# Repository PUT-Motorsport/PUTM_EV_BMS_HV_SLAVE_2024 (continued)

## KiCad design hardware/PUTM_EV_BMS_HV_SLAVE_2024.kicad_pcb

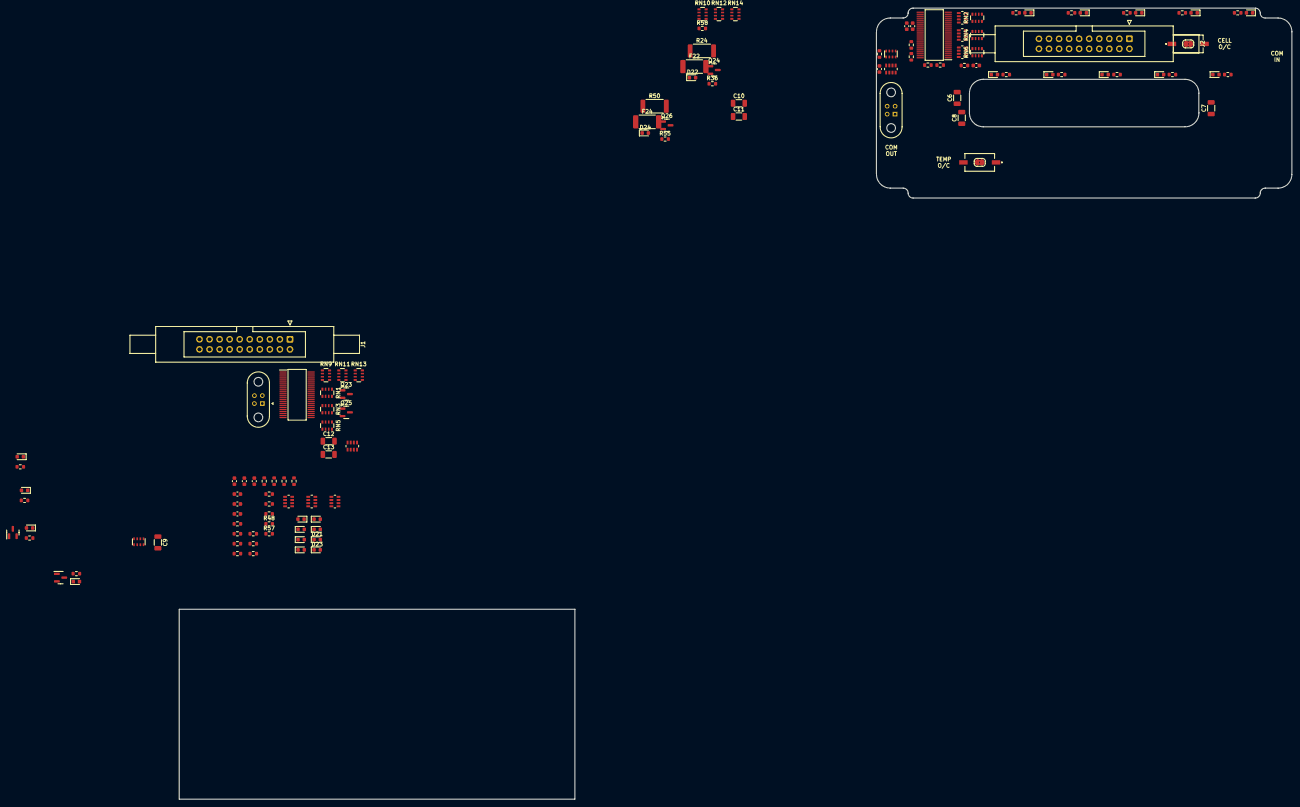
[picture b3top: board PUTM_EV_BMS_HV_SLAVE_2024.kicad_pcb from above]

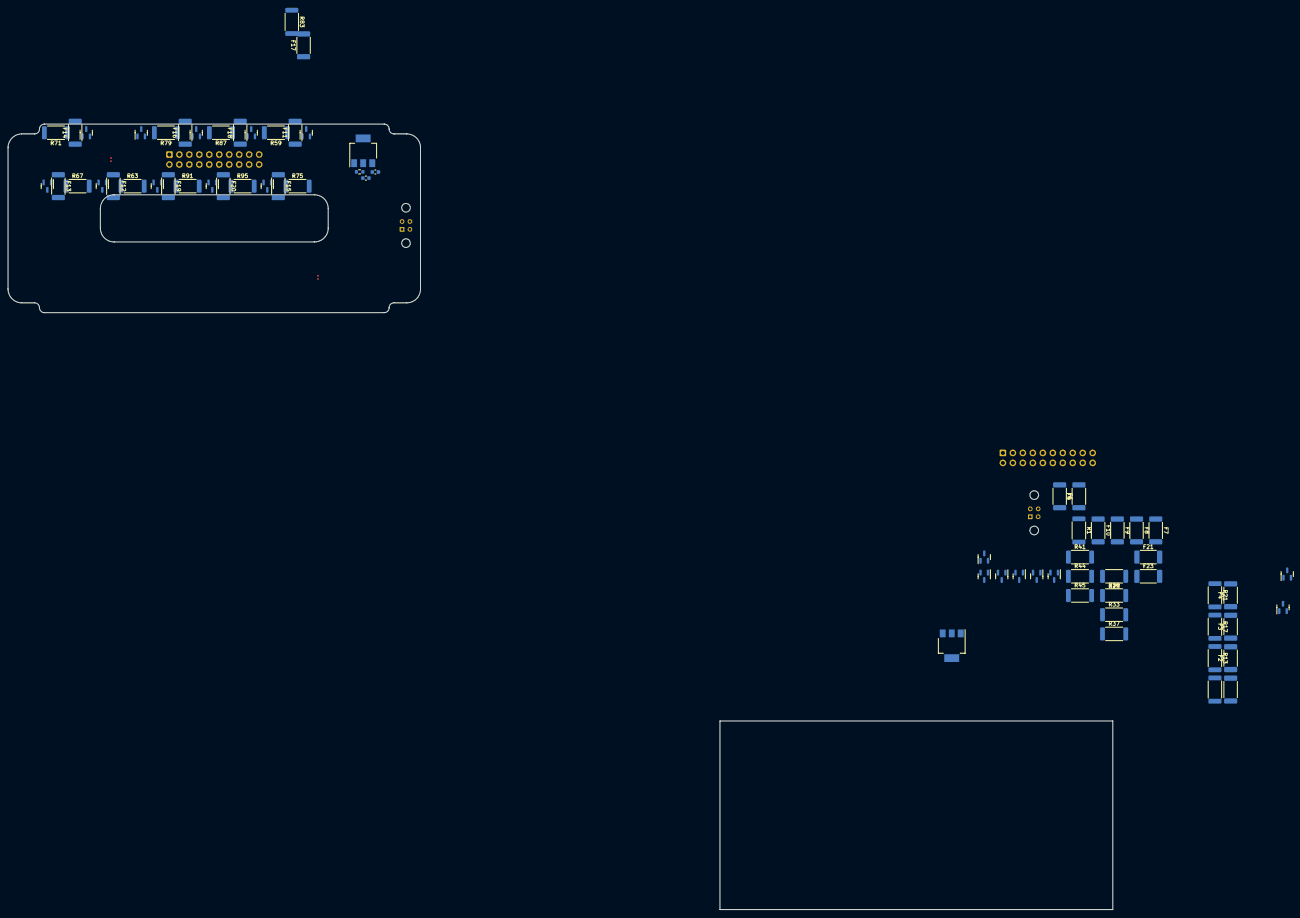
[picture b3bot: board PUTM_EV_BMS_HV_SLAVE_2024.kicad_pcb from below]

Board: 4 copper layers, 281.2 x 199.9 mm, 190 parts (67 on the bottom side), 216 nets, no tracks yet.

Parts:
C1, C2, C3, C21, C22, C23: 1uF; C_0603_1608Metric
C4, C5, C18, C19, C20, C24: 100nF; C_0603_1608Metric
C6, C7, C8, C9, C10, C11, C12, C13: 10nF/1kV; C_1206_3216Metric
CN1, CN2, CN3, CN4, CN5, CN6, CN7, CN8: 4x100nF; CA064X104K4RACAUTO
D1, D2, D3, D4, D5, D6, D7, D8, D9, D10, D11, D12, D13, D14, D15, D16, D17, D18, D19, D20, D21, D22, D23, D24: LED; LED_0603_1608Metric
F1, F2, F3, F4, F5, F6, F7, F8, F9, F10, F11, F12, F13, F14, F15, F16, F17, F18, F19, F20, F21, F22, F23, F24: 1206L600SLWR; Fuse_2512_6332Metric
IC1, IC2: LTC6804HG-1#PBF; SOP50P780X200-48N
J1, J2: TST-110-01-T-D; IDC-Header_2x10_P2.54mm_Latch6.5mm_Vertical
J3, J4: M80-5100442; M80-51004YY
JP1, JP2: MES; SolderJumper-2_P1.3mm_Bridged2Bar_RoundedPad1.0x1.5mm
Q1, Q12: BCP56; SOT-223-3_TabPin2
Q2, Q3, Q4, Q5, Q6, Q7, Q8, Q9, Q10, Q11, Q13, Q14, Q15, Q16, Q17, Q18, Q19, Q20, Q21, Q22, Q23, Q24, Q25, Q26: CPH3351; SOT-23
R1, R9, R13, R17, R21, R24, R25, R29, R33, R37, R41, R44, R45, R50, R59, R63, R67, R71, R75, R79, R83, R87, R91, R95: 15/2W; R_2512_6332Metric
R2, R3: 10k; R_0603_1608Metric
R4, R5, R51, R53, R57, R58: 100; R_0603_1608Metric
R6, R10, R14, R18, R22, R26, R30, R34, R36, R38, R42, R46, R48, R55, R60, R64, R68, R72, R76, R80, R84, R88, R92, R96: 330; R_0603_1608Metric
R7, R8, R52, R54: 1k; R_0603_1608Metric
R12, R20, R28, R32: 120; R_0603_1608Metric
RN1, RN2, RN3, RN4, RN5, RN6: 4x100; R_Array_Convex_4x0603
RN7, RN8: 4x10k; EXBV8V101JV
RN9, RN10, RN11, RN12, RN13, RN14: 4x3.3k; R_Array_Convex_4x0603
S1, S2: A6SN-1104; A6SN1104

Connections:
/C1+: D2.1 (K), J1.3, Q2.2 (S), R13.2, RN3.8 (R1.2)
/C1-: C1.2, C2.2, C3.2, C4.2, C13.2, C18.2, C19.2, CN7.1 (R1.1), CN7.2 (R2.1), CN7.3 (R3.1), CN7.4 (R4.1), D1.1 (K), IC1.30 (V-), IC1.31 (V-), IC1.36 (SWTEN), J1.1, J1.11, J1.12, R8.2, R9.2, R57.1
/C2+: D3.1 (K), J1.7, Q3.2 (S), R17.2, RN3.7 (R2.2)
/C3+: D4.1 (K), J1.17, Q4.2 (S), R21.2, RN3.6 (R3.2)
/C4+: D5.1 (K), J1.19, Q5.2 (S), R25.2, RN3.5 (R4.2)
/C5+: D6.1 (K), J1.20, Q6.2 (S), R29.2, RN1.8 (R1.2)
/C6+: D7.1 (K), J1.18, Q7.2 (S), R33.2, RN1.7 (R2.2)
/C7+: D8.1 (K), J1.16, Q8.2 (S), R37.2, RN1.6 (R3.2)
/C8+: D9.1 (K), J1.8, Q9.2 (S), R41.2, RN1.5 (R4.2)
/C9+: D10.1 (K), J1.4, Q10.2 (S), R45.2, RN5.8 (R1.2)
/C10+: D21.1 (K), J1.2, Q11.2 (S), R1.2, RN5.7 (R2.2)
/C11-: C5.2, C8.2, C20.2, C21.2, C22.2, C23.2, C24.2, CN8.1 (R1.1), CN8.2 (R2.1), CN8.3 (R3.1), CN8.4 (R4.1), D14.1 (K), IC2.30 (V-), IC2.31 (V-), IC2.36 (SWTEN), J2.1, J2.11, J2.12, R54.2, R58.1, R71.2
/C11_SW+: D17.1 (K), Q16.2 (S), R83.2, RN4.8 (R1.2)
/C12+: D16.1 (K), J2.7, Q19.2 (S), R79.2, RN4.7 (R2.2)
/C13+: D18.1 (K), J2.17, Q18.2 (S), R87.2, RN4.6 (R3.2)
/C14+: D11.1 (K), J2.19, Q20.2 (S), R59.2, RN4.5 (R4.2)
/C15+: D15.1 (K), J2.20, Q13.2 (S), R75.2, RN2.8 (R1.2)
/C16+: D20.1 (K), J2.18, Q17.2 (S), R95.2, RN2.7 (R2.2)
/C17+: D19.1 (K), J2.16, Q22.2 (S), R91.2, RN2.6 (R3.2)
/C18+: D12.1 (K), J2.8, Q21.2 (S), R63.2, RN2.5 (R4.2)
/C19+: D13.1 (K), J2.4, Q14.2 (S), R67.2, RN6.8 (R1.2)
/C20+: D22.1 (K), J2.2, Q15.2 (S), R24.2, RN6.7 (R2.2)
/IMA: C12.1, IC1.41 (CSB_(IMA)), R12.2
/IMB: C7.2, IC2.47 (IMB), R32.2
/IN+: C9.2, J4.1
/IN-: C12.2, J4.2
/IPA: C9.1, IC1.42 (SCK(IPA)), R12.1
/IPB: C6.2, IC2.48 (IPB), R32.1
/L_LTC/C0: CN1.8 (R1.2), IC1.26 (C0), R57.2
/L_LTC/C1: CN1.1 (R1.1), CN1.7 (R2.2), IC1.24 (C1), RN3.1 (R1.1)
/L_LTC/C2: CN1.2 (R2.1), CN1.6 (R4.1), IC1.22 (C2), RN3.2 (R2.1)
/L_LTC/C3: CN1.3 (R3.1), CN1.5 (R4.2), IC1.20 (C3), RN3.3 (R3.1)
/L_LTC/C4: CN1.4 (R4.1), CN3.8 (R1.2), IC1.18 (C4), RN3.4 (R4.1)
/L_LTC/C5: CN3.1 (R1.1), CN3.7 (R2.2), IC1.16 (C5), RN1.1 (R1.1)
/L_LTC/C6: CN3.2 (R2.1), CN3.6 (R4.1), IC1.14 (C6), RN1.2 (R2.1)
/L_LTC/C7: CN3.3 (R3.1), CN3.5 (R4.2), IC1.12 (C7), RN1.3 (R3.1)
/L_LTC/C8: CN3.4 (R4.1), CN5.8 (R1.2), IC1.10 (C8), RN1.4 (R4.1)
/L_LTC/C9: CN5.1 (R1.1), CN5.7 (R2.2), IC1.8 (C9), RN5.1 (R1.1)
/L_LTC/C10: CN5.2 (R2.1), CN5.6 (R4.1), IC1.6 (C10), RN5.2 (R2.1)
/L_LTC/C11: CN5.3 (R3.1), CN5.5 (R4.2), IC1.4 (C11), RN5.3 (R3.1)
/L_LTC/C11+: D23.1 (K), Q23.2 (S), R44.2, RN5.6 (R3.2)
/L_LTC/C12: CN5.4 (R4.1), IC1.2 (C12), RN5.4 (R4.1)
/L_LTC/DCH1/S: Q2.1 (G), RN9.8 (R1.2)
/L_LTC/DCH2/S: Q3.1 (G), RN9.7 (R2.2)
/L_LTC/DCH3/S: Q4.1 (G), RN9.6 (R3.2)
/L_LTC/DCH4/S: Q5.1 (G), RN9.5 (R4.2)
/L_LTC/DCH5/S: Q6.1 (G), RN11.8 (R1.2)
/L_LTC/DCH6/S: Q7.1 (G), RN11.7 (R2.2)
/L_LTC/DCH7/S: Q8.1 (G), RN11.6 (R3.2)
/L_LTC/DCH8/S: Q9.1 (G), RN11.5 (R4.2)
/L_LTC/DCH9/S: Q10.1 (G), RN13.8 (R1.2)
/L_LTC/DCH10/S: Q11.1 (G), RN13.7 (R2.2)
/L_LTC/DCH11/S: Q23.1 (G), RN13.6 (R3.2)
/L_LTC/DCH12/S: Q25.1 (G), RN13.5 (R4.2)
/L_LTC/IMB: C11.2, IC1.47 (IMB), R20.2
/L_LTC/IPB: C10.2, IC1.48 (IPB), R20.1
/L_LTC/S1: IC1.25 (S1), RN9.1 (R1.1)
/L_LTC/S2: IC1.23 (S2), RN9.2 (R2.1)
/L_LTC/S3: IC1.21 (S3), RN9.3 (R3.1)
/L_LTC/S4: IC1.19 (S4), RN9.4 (R4.1)
/L_LTC/S5: IC1.17 (S5), RN11.1 (R1.1)
/L_LTC/S6: IC1.15 (S6), RN11.2 (R2.1)
/L_LTC/S7: IC1.13 (S7), RN11.3 (R3.1)
/L_LTC/S8: IC1.11 (S8), RN11.4 (R4.1)
/L_LTC/S9: IC1.9 (S9), RN13.1 (R1.1)
/L_LTC/S10: IC1.7 (S10), RN13.2 (R2.1)
/L_LTC/S11: IC1.5 (S11), RN13.3 (R3.1)
/L_LTC/S12: IC1.3 (S12), RN13.4 (R4.1)
/L_LTC/V+: C19.1, Q25.2 (S), R4.2, R5.1, RN5.5 (R4.2)
/L_LTC/VREF2: C2.1, IC1.35 (VREF1), R2.2, RN7.5 (R4.2), RN7.6 (R3.2), RN7.7 (R2.2), RN7.8 (R1.2)
/L_LTC/VREG: C3.1, IC1.37 (VREG), IC1.40 (ISOMD), Q1.3 (E)
/OUT+: C6.1, J3.1
/OUT-: C7.1, J3.2
/R_LTC/C0: CN2.8 (R1.2), IC2.26 (C0), R58.2
/R_LTC/C1: CN2.1 (R1.1), CN2.7 (R2.2), IC2.24 (C1), RN4.1 (R1.1)
/R_LTC/C2: CN2.2 (R2.1), CN2.6 (R4.1), IC2.22 (C2), RN4.2 (R2.1)
/R_LTC/C3: CN2.3 (R3.1), CN2.5 (R4.2), IC2.20 (C3), RN4.3 (R3.1)
/R_LTC/C4: CN2.4 (R4.1), CN4.8 (R1.2), IC2.18 (C4), RN4.4 (R4.1)
/R_LTC/C5: CN4.1 (R1.1), CN4.7 (R2.2), IC2.16 (C5), RN2.1 (R1.1)
/R_LTC/C6: CN4.2 (R2.1), CN4.6 (R4.1), IC2.14 (C6), RN2.2 (R2.1)
/R_LTC/C7: CN4.3 (R3.1), CN4.5 (R4.2), IC2.12 (C7), RN2.3 (R3.1)
/R_LTC/C8: CN4.4 (R4.1), CN6.8 (R1.2), IC2.10 (C8), RN2.4 (R4.1)
/R_LTC/C9: CN6.1 (R1.1), CN6.7 (R2.2), IC2.8 (C9), RN6.1 (R1.1)
/R_LTC/C10: CN6.2 (R2.1), CN6.6 (R4.1), IC2.6 (C10), RN6.2 (R2.1)
/R_LTC/C11: CN6.3 (R3.1), CN6.5 (R4.2), IC2.4 (C11), RN6.3 (R3.1)
/R_LTC/C11+: D24.1 (K), Q24.2 (S), R50.2, RN6.6 (R3.2)
/R_LTC/C12: CN6.4 (R4.1), IC2.2 (C12), RN6.4 (R4.1)
/R_LTC/DCH1/S: Q16.1 (G), RN10.8 (R1.2)
/R_LTC/DCH2/S: Q19.1 (G), RN10.7 (R2.2)
/R_LTC/DCH3/S: Q18.1 (G), RN10.6 (R3.2)
/R_LTC/DCH4/S: Q20.1 (G), RN10.5 (R4.2)
/R_LTC/DCH5/S: Q13.1 (G), RN12.8 (R1.2)
/R_LTC/DCH6/S: Q17.1 (G), RN12.7 (R2.2)
/R_LTC/DCH7/S: Q22.1 (G), RN12.6 (R3.2)
/R_LTC/DCH8/S: Q21.1 (G), RN12.5 (R4.2)
/R_LTC/DCH9/S: Q14.1 (G), RN14.8 (R1.2)
/R_LTC/DCH10/S: Q15.1 (G), RN14.7 (R2.2)
/R_LTC/DCH11/S: Q24.1 (G), RN14.6 (R3.2)
/R_LTC/DCH12/S: Q26.1 (G), RN14.5 (R4.2)
/R_LTC/IMA: C11.1, IC2.41 (CSB_(IMA)), R28.2
/R_LTC/IPA: C10.1, IC2.42 (SCK(IPA)), R28.1
/R_LTC/S1: IC2.25 (S1), RN10.1 (R1.1)
/R_LTC/S2: IC2.23 (S2), RN10.2 (R2.1)
/R_LTC/S3: IC2.21 (S3), RN10.3 (R3.1)
/R_LTC/S4: IC2.19 (S4), RN10.4 (R4.1)
/R_LTC/S5: IC2.17 (S5), RN12.1 (R1.1)
/R_LTC/S6: IC2.15 (S6), RN12.2 (R2.1)
/R_LTC/S7: IC2.13 (S7), RN12.3 (R3.1)
/R_LTC/S8: IC2.11 (S8), RN12.4 (R4.1)
/R_LTC/S9: IC2.9 (S9), RN14.1 (R1.1)
/R_LTC/S10: IC2.7 (S10), RN14.2 (R2.1)
/R_LTC/S11: IC2.5 (S11), RN14.3 (R3.1)
/R_LTC/S12: IC2.3 (S12), RN14.4 (R4.1)
/R_LTC/V+: C20.1, Q26.2 (S), R51.2, R53.1, RN6.5 (R4.2)
/R_LTC/VREF2: C22.1, IC2.35 (VREF1), R3.2, RN8.5 (R4.2), RN8.6 (R3.2), RN8.7 (R2.2), RN8.8 (R1.2)
/R_LTC/VREG: C23.1, IC2.37 (VREG), IC2.40 (ISOMD), Q12.3 (E)
/TH1+: C4.1, IC1.27 (GPIO1), J1.5, R2.1
/TH2+: CN7.8 (R1.2), IC1.28 (GPIO2), J1.9, RN7.1 (R1.1)
/TH3_SW+: CN7.7 (R2.2), IC1.29 (GPIO3), RN7.2 (R2.1)
/TH4+: CN7.6 (R3.2), IC1.32 (GPIO4), J1.14, RN7.3 (R3.1)
/TH5+: CN7.5 (R4.2), IC1.33 (GPIO5), J1.10, RN7.4 (R4.1)
/TH6+: C5.1, IC2.27 (GPIO1), J2.5, R3.1
/TH7+: CN8.8 (R1.2), IC2.28 (GPIO2), J2.9, RN8.1 (R1.1)
/TH8+: CN8.7 (R2.2), IC2.29 (GPIO3), J2.15, RN8.2 (R2.1)
/TH9+: CN8.6 (R3.2), IC2.32 (GPIO4), J2.14, RN8.3 (R3.1)
/TH10+: CN8.5 (R4.2), IC2.33 (GPIO5), J2.10, RN8.4 (R4.1)
unnamed: D1.2 (A), R10.2
unnamed: D2.2 (A), R14.2
unnamed: D3.2 (A), R18.2
unnamed: D4.2 (A), R22.2
unnamed: D5.2 (A), R26.2
unnamed: D6.2 (A), R30.2
unnamed: D7.2 (A), R34.2
unnamed: D8.2 (A), R38.2
unnamed: D9.2 (A), R42.2
unnamed: D10.2 (A), R46.2
unnamed: D11.2 (A), R60.2
unnamed: D12.2 (A), R64.2
unnamed: D13.2 (A), R68.2
unnamed: D14.2 (A), R72.2
unnamed: D15.2 (A), R76.2
unnamed: D16.2 (A), R80.2
unnamed: D17.2 (A), R84.2
unnamed: D18.2 (A), R88.2
unnamed: D19.2 (A), R92.2
unnamed: D20.2 (A), R96.2
unnamed: D21.2 (A), R6.2
unnamed: D22.2 (A), R36.2
unnamed: D23.2 (A), R48.2
unnamed: D24.2 (A), R55.2
unnamed: F1.1, R9.1, R10.1
unnamed: F2.1, R13.1, R14.1
unnamed: F3.1, R17.1, R18.1
unnamed: F4.1, R21.1, R22.1
unnamed: F5.1, R25.1, R26.1
unnamed: F6.1, R29.1, R30.1
unnamed: F7.1, R33.1, R34.1
unnamed: F8.1, R37.1, R38.1
unnamed: F9.1, R41.1, R42.1
unnamed: F10.1, R45.1, R46.1
unnamed: F11.1, R59.1, R60.1
unnamed: F12.1, R63.1, R64.1
unnamed: F13.1, R67.1, R68.1
unnamed: F14.1, R71.1, R72.1
unnamed: F15.1, R75.1, R76.1
unnamed: F16.1, R79.1, R80.1
unnamed: F17.1, R83.1, R84.1
unnamed: F18.1, R87.1, R88.1
unnamed: F19.1, R91.1, R92.1
unnamed: F20.1, R95.1, R96.1
unnamed: F21.1, R1.1, R6.1
unnamed: F22.1, R24.1, R36.1
unnamed: F23.1, R44.1, R48.1
unnamed: F24.1, R50.1, R55.1
unnamed: IC1.38 (DRIVE), Q1.1 (B)
unnamed: IC1.45 (IBIAS), R7.1
unnamed: IC1.46 (ICMP), R7.2, R8.1
unnamed: IC1.1 (V+), R4.1
unnamed: C1.1, IC1.34 (VREF2)
unnamed: IC2.38 (DRIVE), Q12.1 (B)
unnamed: IC2.45 (IBIAS), R52.1
unnamed: IC2.46 (ICMP), R52.2, R54.1
unnamed: IC2.1 (V+), R51.1
unnamed: C21.1, IC2.34 (VREF2)
unnamed: C8.1, J3.3, J3.4
unnamed: C13.1, J4.3, J4.4
unnamed: JP1.1 (A), S1.1
unnamed: JP1.2 (B), S1.2
unnamed: JP2.1 (A), S2.1
unnamed: JP2.2 (B), S2.2
unnamed: C18.1, Q1.2 (C), R5.2
unnamed: F1.2, Q2.3 (D)
unnamed: F2.2, Q3.3 (D)
unnamed: F3.2, Q4.3 (D)
unnamed: F4.2, Q5.3 (D)
unnamed: F5.2, Q6.3 (D)
unnamed: F6.2, Q7.3 (D)
unnamed: F7.2, Q8.3 (D)
unnamed: F8.2, Q9.3 (D)
unnamed: F9.2, Q10.3 (D)
unnamed: F10.2, Q11.3 (D)
unnamed: C24.1, Q12.2 (C), R53.2
unnamed: F11.2, Q13.3 (D)
unnamed: F12.2, Q14.3 (D)
unnamed: F13.2, Q15.3 (D)
unnamed: F14.2, Q16.3 (D)
unnamed: F15.2, Q17.3 (D)
unnamed: F16.2, Q18.3 (D)
unnamed: F17.2, Q19.3 (D)
unnamed: F18.2, Q20.3 (D)
unnamed: F19.2, Q21.3 (D)
unnamed: F20.2, Q22.3 (D)
unnamed: F21.2, Q23.3 (D)
unnamed: F22.2, Q24.3 (D)
unnamed: F23.2, Q25.3 (D)
unnamed: F24.2, Q26.3 (D)

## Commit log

2023-10-30 v2.0.1 testing designs
2023-11-14 spaced out version
2023-11-21 finished layout
2023-11-24 final version
2024-06-03 change from transformator to capacitive isolation between ltc, change ibias/icmp pin since they are incorrectly connected
2024-07-15 new 1.2 revision
2024-07-25 added temp disconnect, beautify schematic
2024-08-04 replaced signal transformer with rated capacitors, made the design more general for future use
2024-08-20 Update README.md
    redme
2024-10-11 notes update
2024-10-11 new schematic
2024-10-19 pending
2024-10-29 layout done
2024-11-02 Bq ic balancing and measureing schematic part + main connector
2024-11-08 sync
2024-11-12 changed back harwin connectors, COM first fitting
2024-11-17 some visual touch ups, added aux diodes for checking comm with IC, temp meas section, fliped the connector to the other side etc.
2024-11-18 pcb layout 99.9% done - all sections named and placed also some initial routing
2024-11-18 routing 80-90% done
2024-11-19 v2.0.0b done
2024-11-20 new balancing schematic
2024-11-21 rounting + layout
2024-11-21 done
2024-12-10 ltc rounting small fix
2024-12-14 last fix
2024-12-15 bom update
2025-05-19 v2.0.1b
2025-05-28 production:
2025-09-01 removed cmc, added tvs on com channels
2026-03-21 dev-hard-v3.0
2026-03-24 slight fixes
2026-03-28 production
